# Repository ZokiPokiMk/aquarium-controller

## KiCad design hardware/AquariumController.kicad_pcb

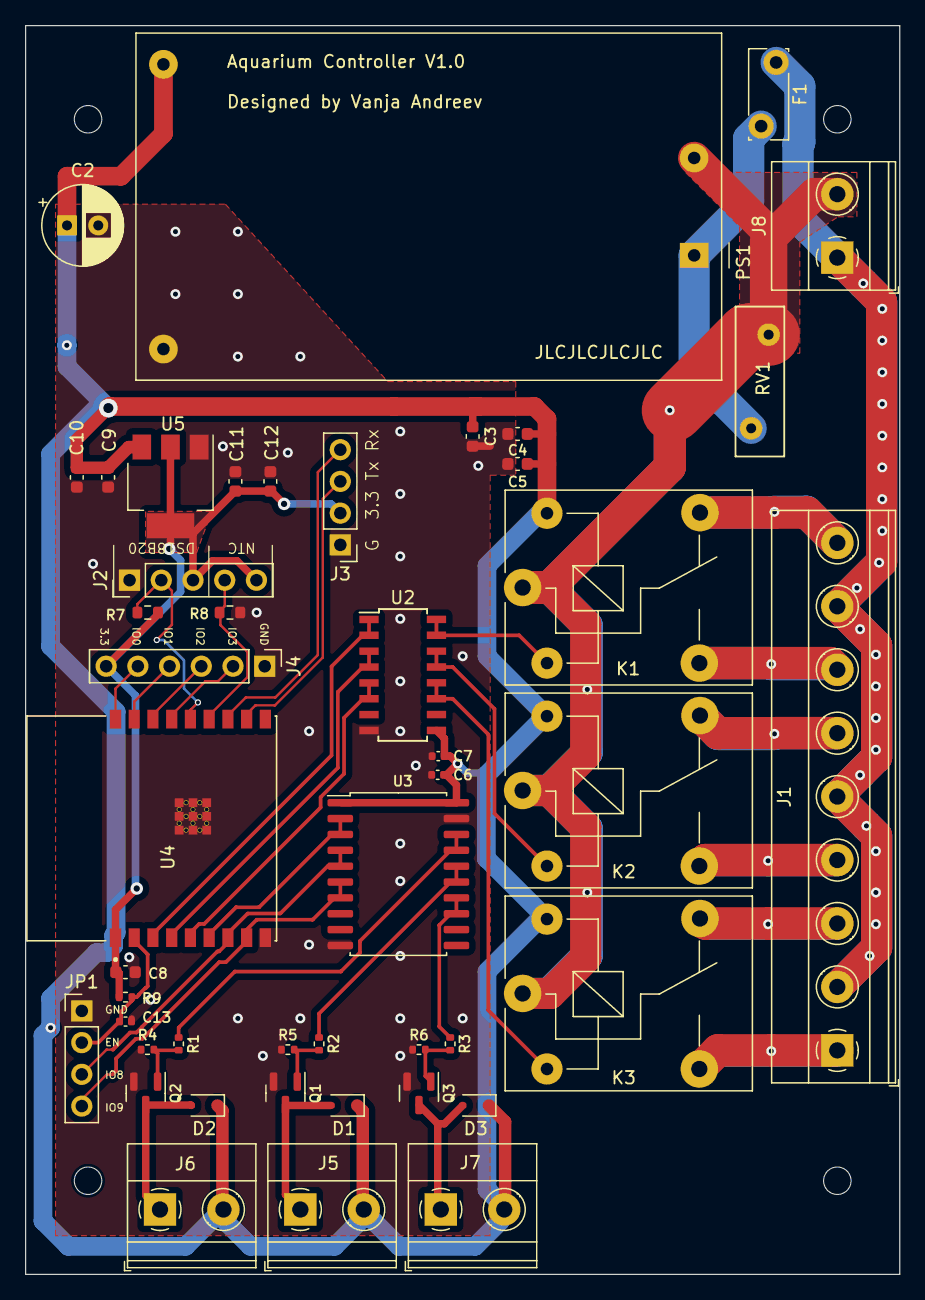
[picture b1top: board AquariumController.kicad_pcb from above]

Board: 2 copper layers, 70.0 x 100.0 mm, 52 parts (0 on the bottom side), 41 nets.

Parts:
C2: 220uF; CP_Radial_D6.3mm_P2.50mm
C3, C4, C5, C9, C12: 10uF; C_0603_1608Metric
C6, C7, C13: 1uF; C_0402_1005Metric
C8: 1uF; C_0603_1608Metric
C10, C11: 0.1uF; C_0603_1608Metric
D1, D2, D3: 1N4148WS; D_SOD-323
F1: 0.5A; Fuse_Bourns_MF-RG300
H1, H2, H3, H4: MountingHole; MountingHole_2.2mm_M2
J1: Conn_01x07; TerminalBlock_Phoenix_MKDS-1,5-9-5.08_1x09_P5.08mm_Horizont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
J2: Conn_01x03; PinHeader_1x05_P2.54mm_Vertical
J3: Conn_01x04; PinHeader_1x04_P2.54mm_Vertical
J4: Conn_01x04; PinHeader_1x06_P2.54mm_Vertical
J5, J6, J7, J8: Conn_01x02; TerminalBlock_Phoenix_MKDS-1,5-2-5.08_1x02_P5.08mm_Horizont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
JP1: rst; PinHeader_1x04_P2.54mm_Vertical
K1, K2, K3: SANYOU_SRD_Form_C; Relay_SPDT_SANYOU_SRD_Series_Form_C
NT1, NT2: NetTie-2_SMD_Pad0.2mm
PS1: HLK-PM01; Converter_ACDC_HiLink_HLK-10Mxx
Q1, Q2, Q3: AO3400A; SOT-23
R1, R2, R3: 100; R_0402_1005Metric
R4, R5, R6, R9: 10K; R_0402_1005Metric
R7, R8: 4K7; R_0603_1608Metric
RV1: 10D561; RV_Disc_D12mm_W3.9mm_P7.5mm
U2: ULN2003; SOIC-16W_ULN2003ADR
U3: 74HC245; SOIC-20W_7.5x12.8mm_P1.27mm
U4: ESP32-C3-WROOM-02-N4; MODULE_ESP32-C3-WROOM-02-H4
U5: AMS1117-3.3; SOT-223-3_TabPin2

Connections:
+3.3V: C8.2, C11.1, C12.1, J2.3, J2.5, J3.2, J4.6, R7.1, R9.1, U4.1 (3V3), U5.2 (VO)
+5V: C2.1, C3.1, C4.1, C5.1, C6.2, C7.2, C9.1, C10.1, D1.1 (K), D2.1 (K), D3.1 (K), J5.2, J6.2, J7.2, K1.5, K2.5, K3.5, PS1.4 (+Vout), U2.9 (COM), U3.1 (A->B), U3.20 (VCC), U5.3 (VI)
/EN: C13.2, JP1.2 (B), R9.2, U4.2 (EN)
/IO0: J4.5, U4.18 (IO0)
/IO1: J4.4, U4.17 (IO1)
/IO2: J4.3, U4.16 (IO2)
/IO3: J4.2, U4.15 (IO3)
/IO8: JP1.3 (C), NT1.2
/IO9: JP1.4 (D), NT2.2
/RS1: NT2.1, U3.6 (A4), U3.7 (A5), U4.8 (IO9)
/RS2: NT1.1, U3.4 (A2), U3.5 (A3), U4.7 (IO8)
/RS3: U3.2 (A0), U3.3 (A1), U4.6 (IO7)
/RS5: U2.5 (I5), U2.6 (I6), U4.5 (IO6)
/RS6: U2.3 (I3), U2.4 (I4), U4.4 (IO5)
/RS7: U2.1 (I1), U2.2 (I2), U4.3 (IO4)
/RX: J3.4, U4.12 (TXD)
/Relay1/NC: J1.7, K1.3
/Relay1/NO: J1.9, K1.4
/Relay2/NC: J1.4, K2.3
/Relay2/NO: J1.6, K2.4
/Relay3/NC: J1.1, K3.3
/Relay3/NO: J1.3, K3.4
/TS1: J2.4, R8.1, U4.13 (IO18)
/TS2: J2.2, R7.2, U4.14 (IO19)
/TX: J3.3, U4.11 (RXD)
/rel1: K1.2, U2.15 (O2), U2.16 (O1)
/rel2: K2.2, U2.13 (O4), U2.14 (O3)
/rel3: K3.2, U2.11 (O6), U2.12 (O5)
/rel5: R1.1, U3.17 (B1), U3.18 (B0)
/rel6: R2.1, U3.15 (B3), U3.16 (B2)
/rel7: R3.1, U3.13 (B5), U3.14 (B4)
AL/L: F1.1, J1.2, J1.5, J1.8, J8.1
AL/N: J8.2, K1.1, K2.1, K3.1, PS1.2 (AC/N), RV1.1
GND: C2.2, C3.2, C4.2, C5.2, C6.1, C7.1, C8.1, C9.2, C10.2, C11.2, C12.2, C13.1, J2.1, J3.1, J4.1, JP1.1 (A), PS1.3 (-Vout), Q1.2 (S), Q2.2 (S), Q3.2 (S), R4.1, R5.1, R6.1, R8.2, U2.8 (GND), U3.10 (GND), U3.19 (CE), U4.9 (GND), U4.19 (GND), U4.20 (GND), U4.21 (GND), U4.22 (GND), U4.23 (GND), U4.24 (GND), U4.25 (GND), U4.26 (GND), U4.27 (GND), U4.28 (GND), U4.29 (GND), U4.30 (GND), U4.31 (GND), U4.32 (GND), U4.33 (GND), U4.34 (GND), U4.35 (GND), U4.36 (GND), U4.37 (GND), U4.38 (GND), U4.39 (GND), U5.1 (GND)
unnamed: D1.2 (A), J5.1, Q1.3 (D)
unnamed: D2.2 (A), J6.1, Q2.3 (D)
unnamed: D3.2 (A), J7.1, Q3.3 (D)
unnamed: F1.2, PS1.1 (AC/L), RV1.2
unnamed: Q1.1 (G), R2.2, R5.2
unnamed: Q2.1 (G), R1.2, R4.2
unnamed: Q3.1 (G), R3.2, R6.2

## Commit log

2023-03-12 rename folder to hardware
2023-03-12 added C13 on EN
2023-03-12 NT1 move
2023-04-23 7.0.1-> 7.0.2, varistor update from library, temporary disable SPICE model issue violation
